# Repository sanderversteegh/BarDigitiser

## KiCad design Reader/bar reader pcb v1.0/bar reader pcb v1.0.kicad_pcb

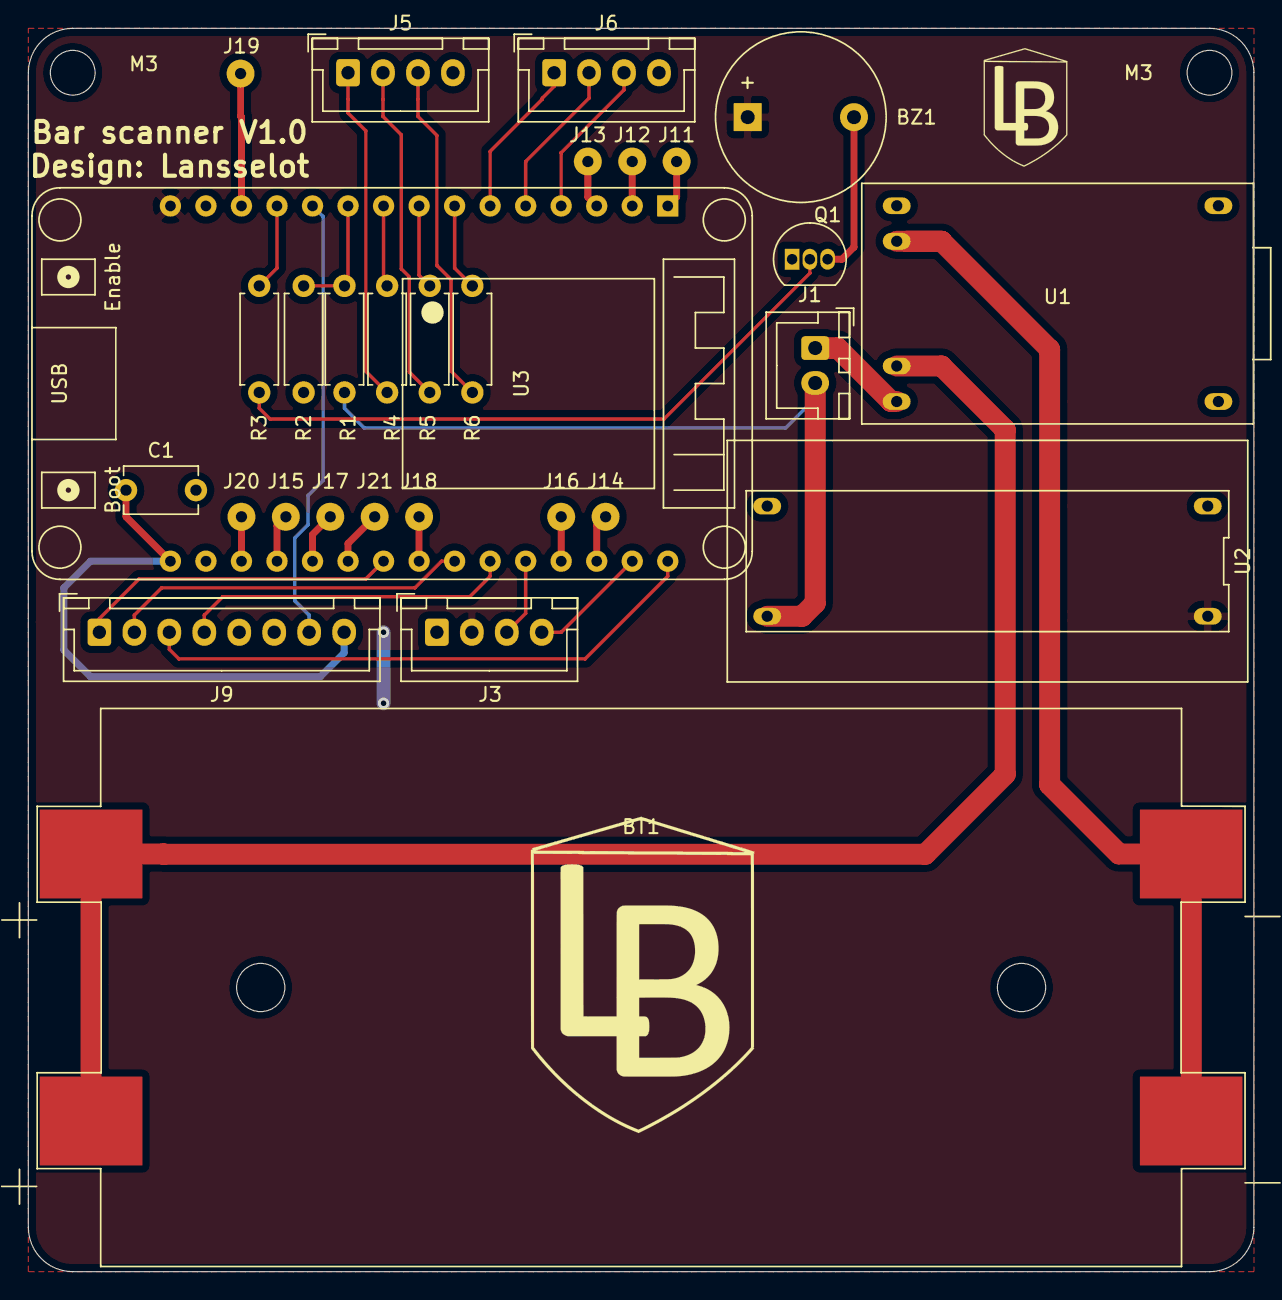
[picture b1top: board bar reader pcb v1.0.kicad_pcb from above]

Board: 2 copper layers, 87.6 x 88.9 mm, 31 parts (0 on the bottom side), 38 nets.

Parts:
BT1: Battery_Cell_2x; BatteryHolder_Keystone_1042_2x18650
BZ1: Buzzer; Buzzer_12x9.5RM7.6
C1: 0,1uf; C_Disc_D5.1mm_W3.2mm_P5.00mm
J1: Conn_01x02_Male; JST_XH_B2B-XH-A_1x02_P2.50mm_Vertical
J3, J5, J6: Conn_01x04_Male; JST_XH_B4B-XH-A_1x04_P2.50mm_Vertical
J9: Conn_01x08_Male; JST_XH_B8B-XH-A_1x08_P2.50mm_Vertical
J11, J12, J13, J14, J15, J16, J17, J18, J19, J20, J21: Conn_01x01_Female; SolderWirePad_1x01_Drill0.8mm
M3, M3#2: MountingHole_3.2mm_M3_DIN965
Q1: PN2222A; TO-92_Inline
R1: 17K; R_Axial_DIN0207_L6.3mm_D2.5mm_P7.62mm_Horizontal
R2: 220; R_Axial_DIN0207_L6.3mm_D2.5mm_P7.62mm_Horizontal
R3: 47K; R_Axial_DIN0207_L6.3mm_D2.5mm_P7.62mm_Horizontal
R4, R5, R6: 48; R_Axial_DIN0207_L6.3mm_D2.5mm_P7.62mm_Horizontal
U1: 1S_BMS_5v-in
U2: MT3608_DC-DC_Boost_5-28V_2A; MT3068_DC-DC_max28V_2A
U3: ESP32_DevKit_V1_DOIT; esp32_devkit_v1_doit

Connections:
+3V3: C1.1, J9.8, U3.16
+5V: BZ1.1, J3.2, U2.1, U3.15
+BATT: BT1.1, BT1.3, U1.5
-BATT: BT1.2, BT1.4, U1.6
GND: C1.2, J3.1, J5.4, J6.4, J9.6, Q1.1, R3.1, U1.4, U2.2, U2.4, U3.14, U3.17
IO12: R2.1, U3.12
IO25: R5.1, U3.8
IO26: R4.1, U3.9
IO27: R1.1, R3.2, U3.10
IO32: J6.1, U3.6
IO33: R6.1, U3.7
IO34: J6.3, U3.4
IO35: J6.2, U3.5
MISO: J9.4, U3.25
MOSI: J9.3, U3.30
unnamed: BZ1.2, Q1.3
unnamed: J5.1, R4.2
unnamed: J5.2, R5.2
unnamed: J5.3, R6.2
unnamed: J11.1, U3.1
unnamed: J12.1, U3.2
unnamed: J13.1, U3.3
unnamed: J14.1, U3.28
unnamed: J15.1, U3.19
unnamed: J16.1, U3.27
unnamed: J17.1, U3.20
unnamed: J18.1, U3.23
unnamed: J19.1, U3.13
unnamed: J20.1, U3.18
unnamed: J21.1, U3.21
unnamed: Q1.2, R2.2
Out+: J1.1, U1.3
OutSwitcht: J1.2, R1.2, U2.3
RST: J9.7, U3.11
SCK: J9.2, U3.24
SCL: J3.4, U3.29
SDA: J3.3, U3.26
SS: J9.1, U3.22

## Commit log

2021-09-07 Create Plugin
2021-09-07 Create ESP32
2021-09-07 Create BarTender
2021-09-07 Create BarApp
2021-09-07 Update and rename BarApp to README
2021-09-07 Update and rename BarTender to README
2021-09-07 Rename ESP32 to README
2021-09-07 Rename Plugin to README
2021-09-07 Rename ESP32/README to Reader/README
